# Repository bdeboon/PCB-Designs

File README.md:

# PCB-Designs
Repo for some of the open-source PCB's I have made over the years.

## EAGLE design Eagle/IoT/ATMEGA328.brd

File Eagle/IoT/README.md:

## IoT board for small wifi projects.

Board dimension = 2.5cm x 2.5cm, comes with wifi adapter, FTDI, USB C Connector for power with an onboard 3.3V regulator.
Assortment of pins can be used to control IoT devices

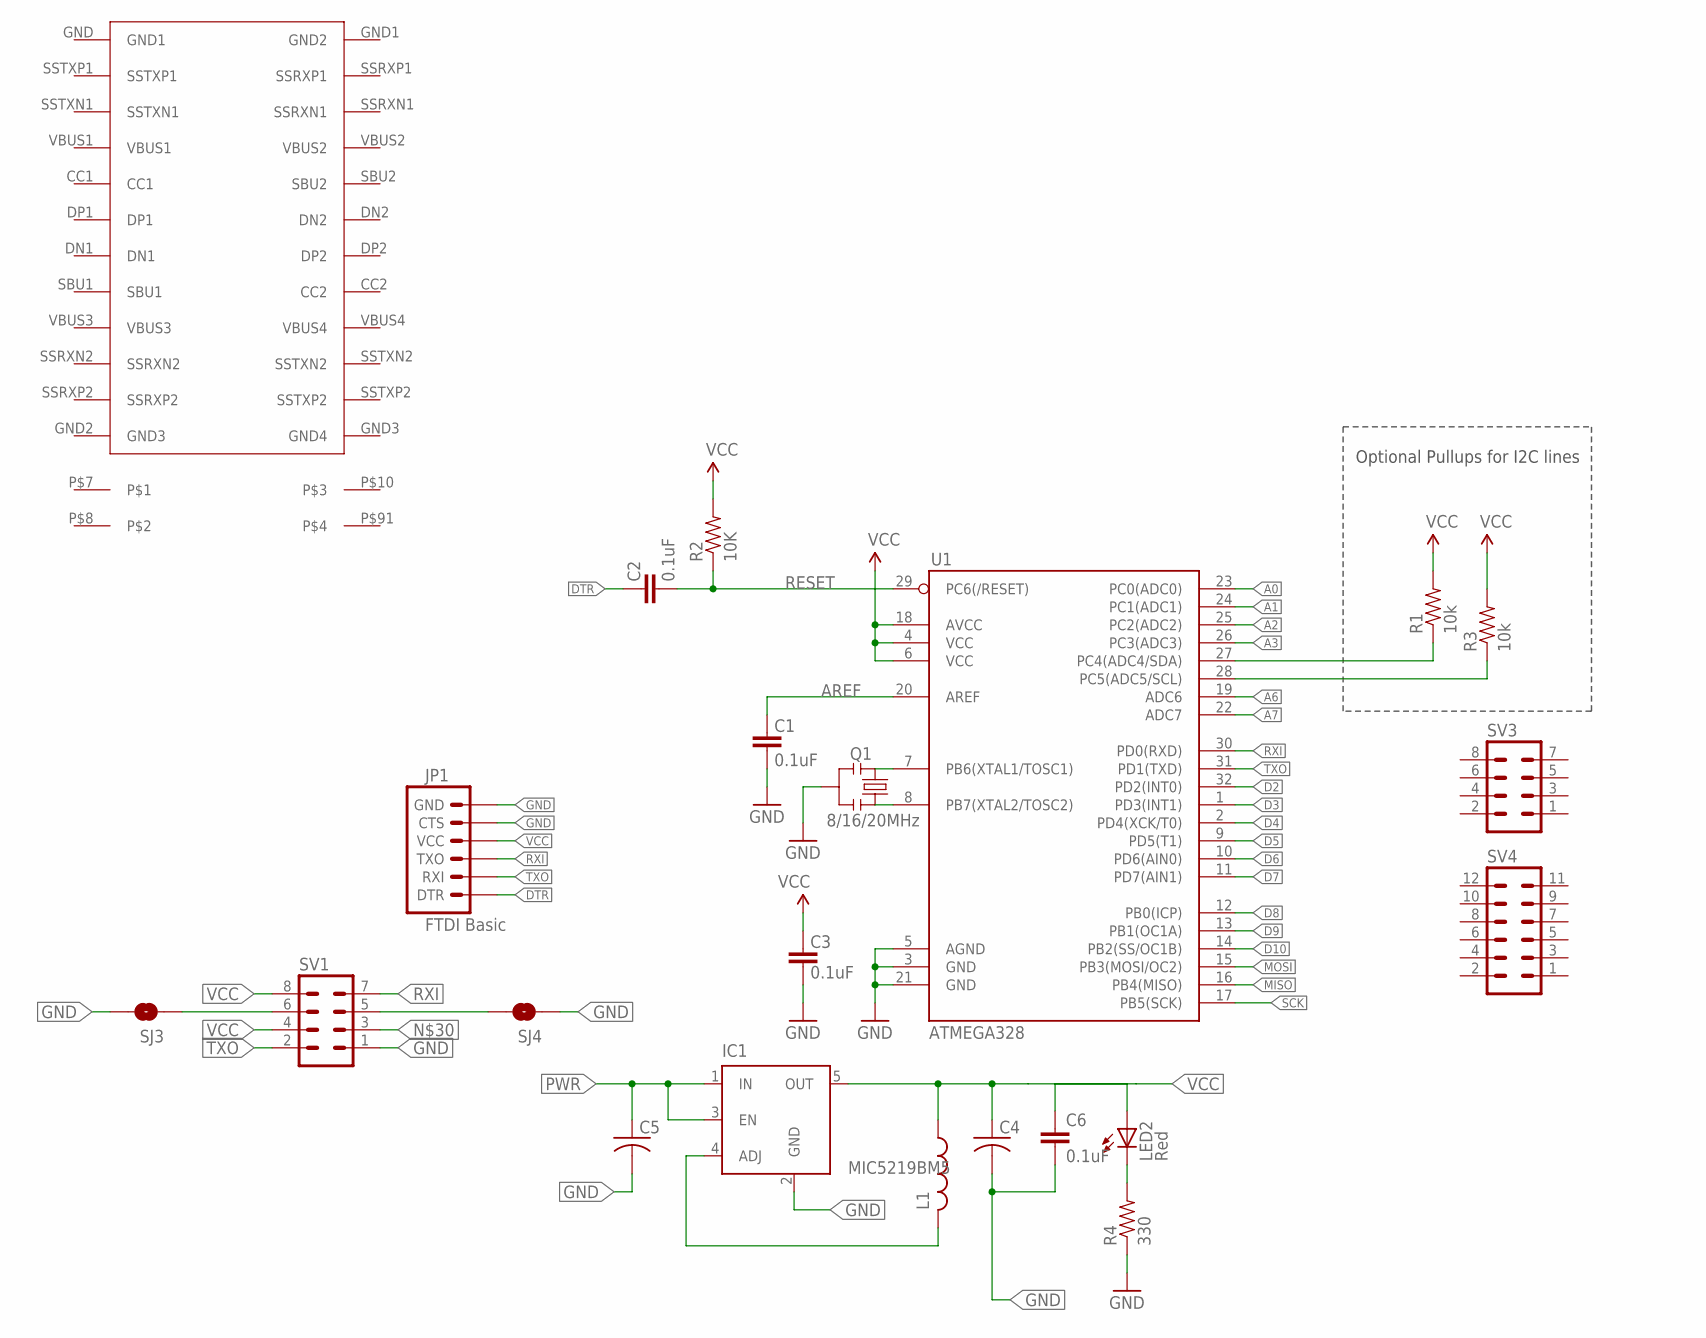
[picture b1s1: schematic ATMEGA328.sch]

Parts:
C1, C2, C3, C6: 0.1uF; 0603-CAP
C4, C5: C-USC0805K; C0805K
IC1: MIC5219BM5; SOT23-5
JP1: FTDI Basic; 1X06
L1: L-USL2012C; L2012C
LED2: Red; 0603-LED-ALT1
Q1: 8/16/20MHz; RESONATOR-SMD-1:1
R1, R3: 10k; 0603-RES
R2: 10K; 0603-RES
R4: 330; 0603-RES
SJ3, SJ4: SOLDERJUMPERNC; SJ_2S
SV1, SV3: MA04-2
SV4: MA06-2
U1: ATMEGA328; TQFP32-08
U$1: USB-C

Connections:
A0: U1.23 (PC0(ADC0))
A1: U1.24 (PC1(ADC1))
A2: U1.25 (PC2(ADC2))
A3: U1.26 (PC3(ADC3))
A4: R1.1, U1.27 (PC4(ADC4/SDA))
A5: R3.1, U1.28 (PC5(ADC5/SCL))
A6: U1.19 (ADC6)
A7: U1.22 (ADC7)
AREF: C1.2, U1.20 (AREF)
D2: U1.32 (PD2(INT0))
D3: U1.1 (PD3(INT1))
D4: U1.2 (PD4(XCK/T0))
D5: U1.9 (PD5(T1))
D6: U1.10 (PD6(AIN0))
D7: U1.11 (PD7(AIN1))
D8: U1.12 (PB0(ICP))
D9: U1.13 (PB1(OC1A))
D10: U1.14 (PB2(SS/OC1B))
DTR: C2.2, JP1.1 (DTR)
GND: C1.1, C3.1, C4.2, C5.2, C6.2, IC1.2 (GND), JP1.5 (CTS), JP1.6 (GND), Q1.2, R4.1, SJ3.2, SJ4.1, SV1.1, U1.3 (GND), U1.5 (AGND), U1.21 (GND)
MISO: U1.16 (PB4(MISO))
MOSI: U1.15 (PB3(MOSI/OC2))
unnamed: Q1.3, U1.8 (PB7(XTAL2/TOSC2))
unnamed: Q1.1, U1.7 (PB6(XTAL1/TOSC1))
unnamed: LED2.C, R4.2
unnamed: SJ4.2, SV1.5
unnamed: IC1.4 (ADJ), L1.2
PWR: C5.1, IC1.1 (IN), IC1.3 (EN)
RESET: C2.1, R2.1, U1.29 (PC6(/RESET))
RESET_WIFI: SJ3.1, SV1.6
RXI: JP1.3 (TXO), SV1.7, U1.30 (PD0(RXD))
SCK: U1.17 (PB5(SCK))
TXO: JP1.2 (RXI), SV1.2, U1.31 (PD1(TXD))
VCC: C3.2, C4.1, C6.1, IC1.5 (OUT), JP1.4 (VCC), L1.1, LED2.A, R1.2, R2.2, R3.2, SV1.4, SV1.8, U1.4 (VCC), U1.6 (VCC), U1.18 (AVCC)

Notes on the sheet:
Optional Pullups for I2C lines

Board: 2 copper layers, 22 parts (0 on the bottom side), 16 nets, no tracks yet.

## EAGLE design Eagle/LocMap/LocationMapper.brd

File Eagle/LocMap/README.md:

# Location Mapper PCB Version 1

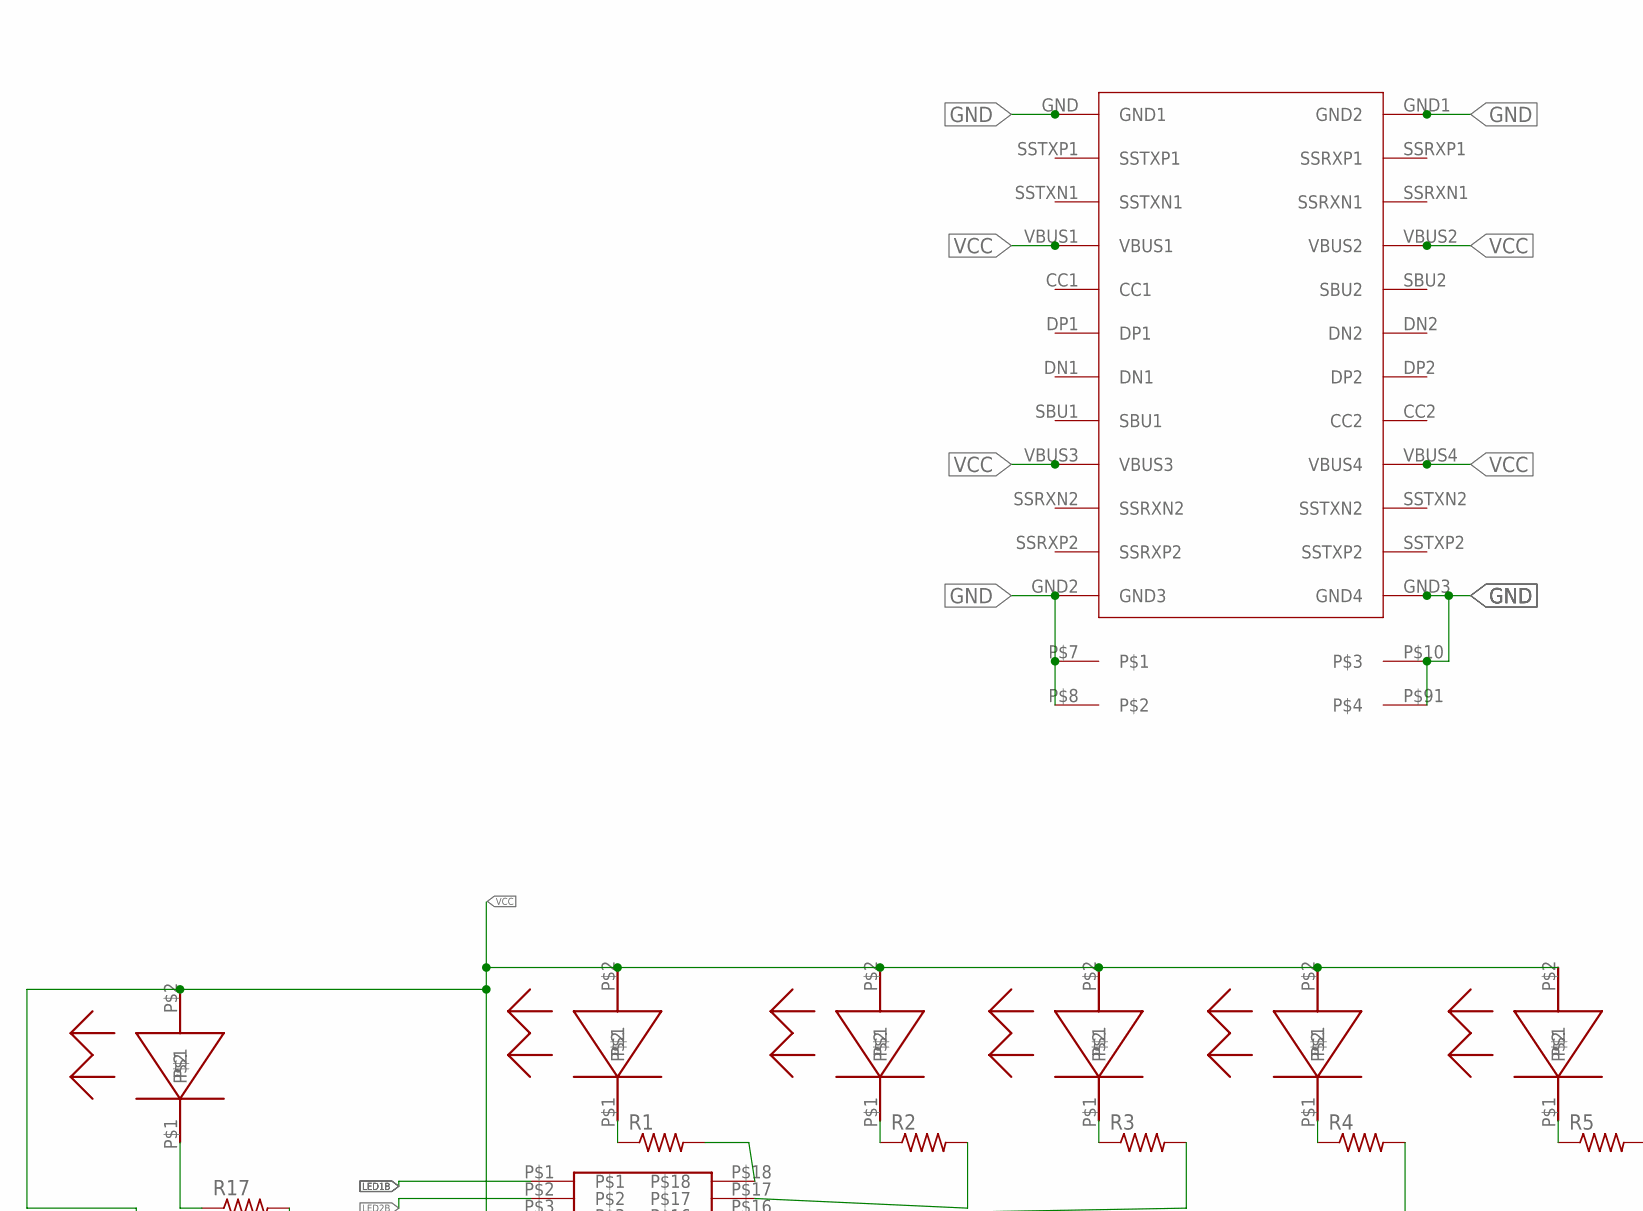
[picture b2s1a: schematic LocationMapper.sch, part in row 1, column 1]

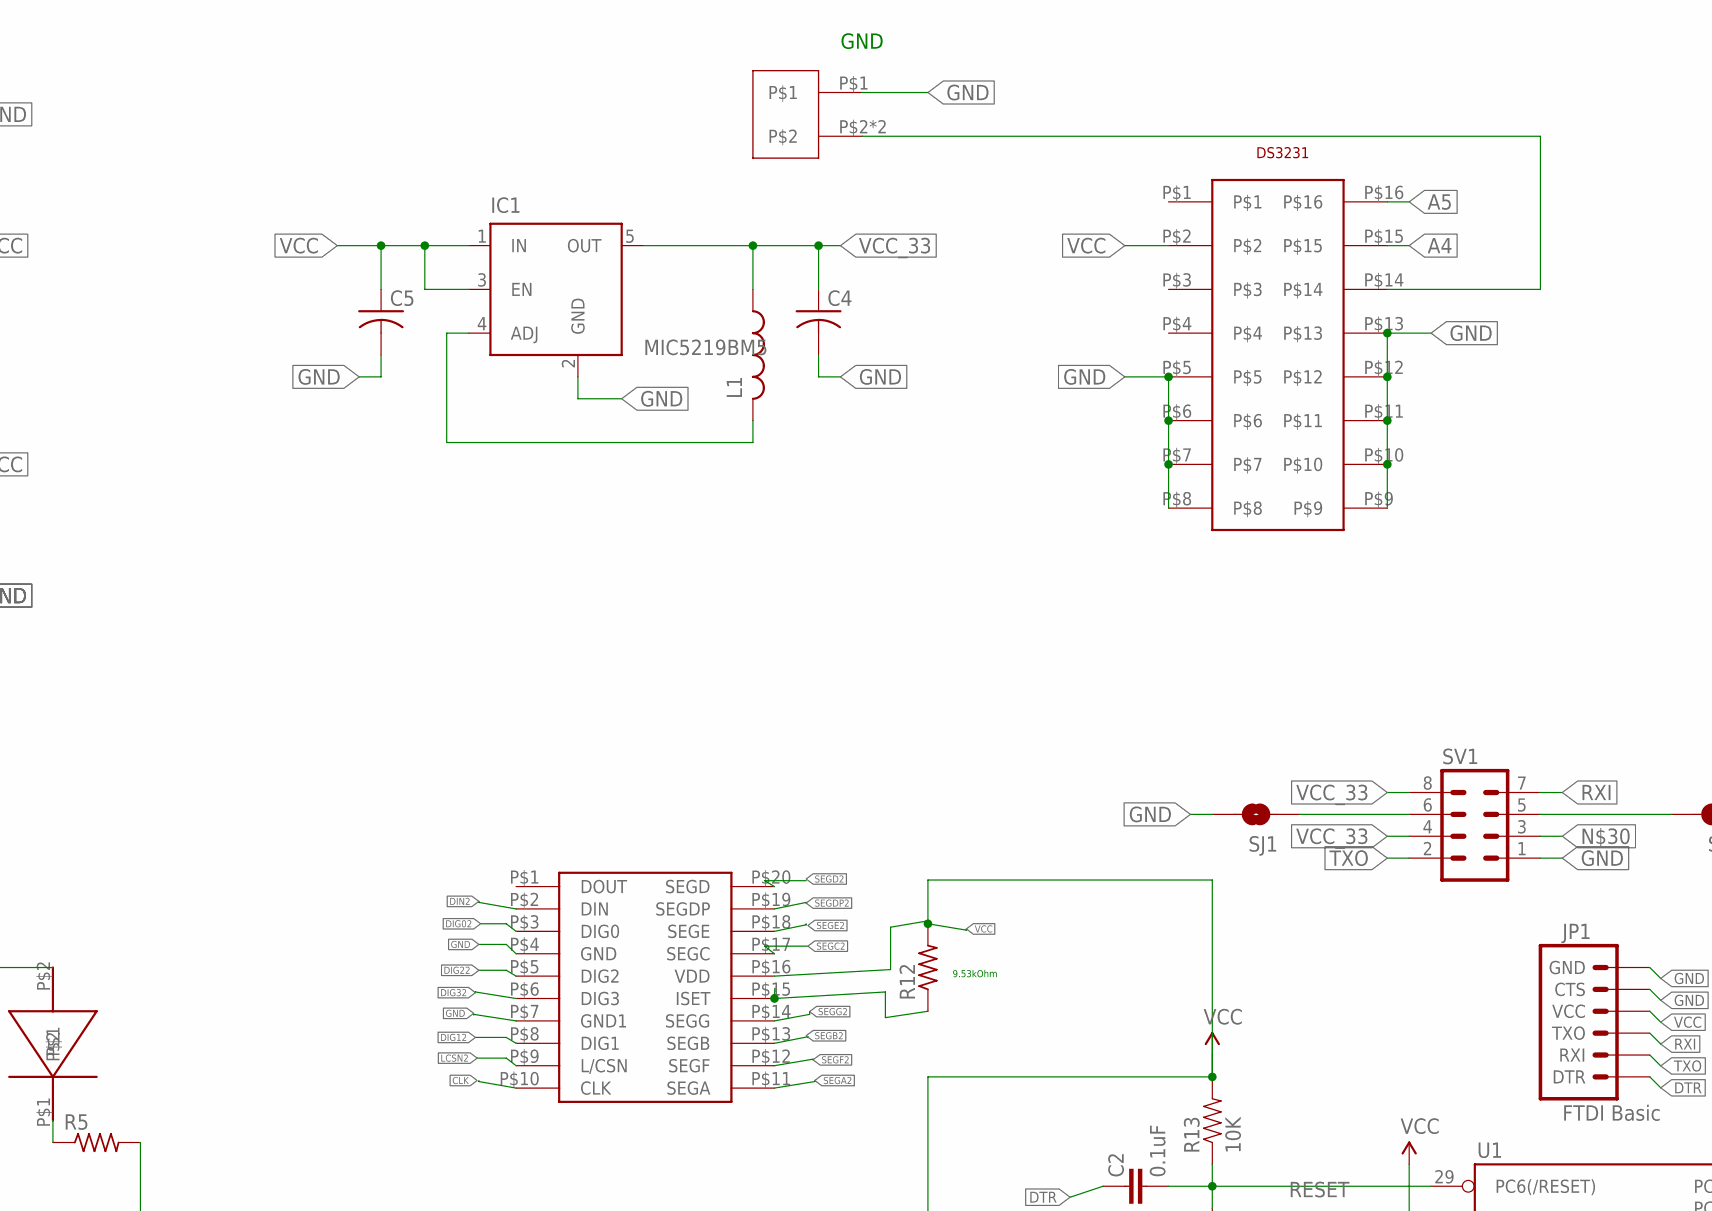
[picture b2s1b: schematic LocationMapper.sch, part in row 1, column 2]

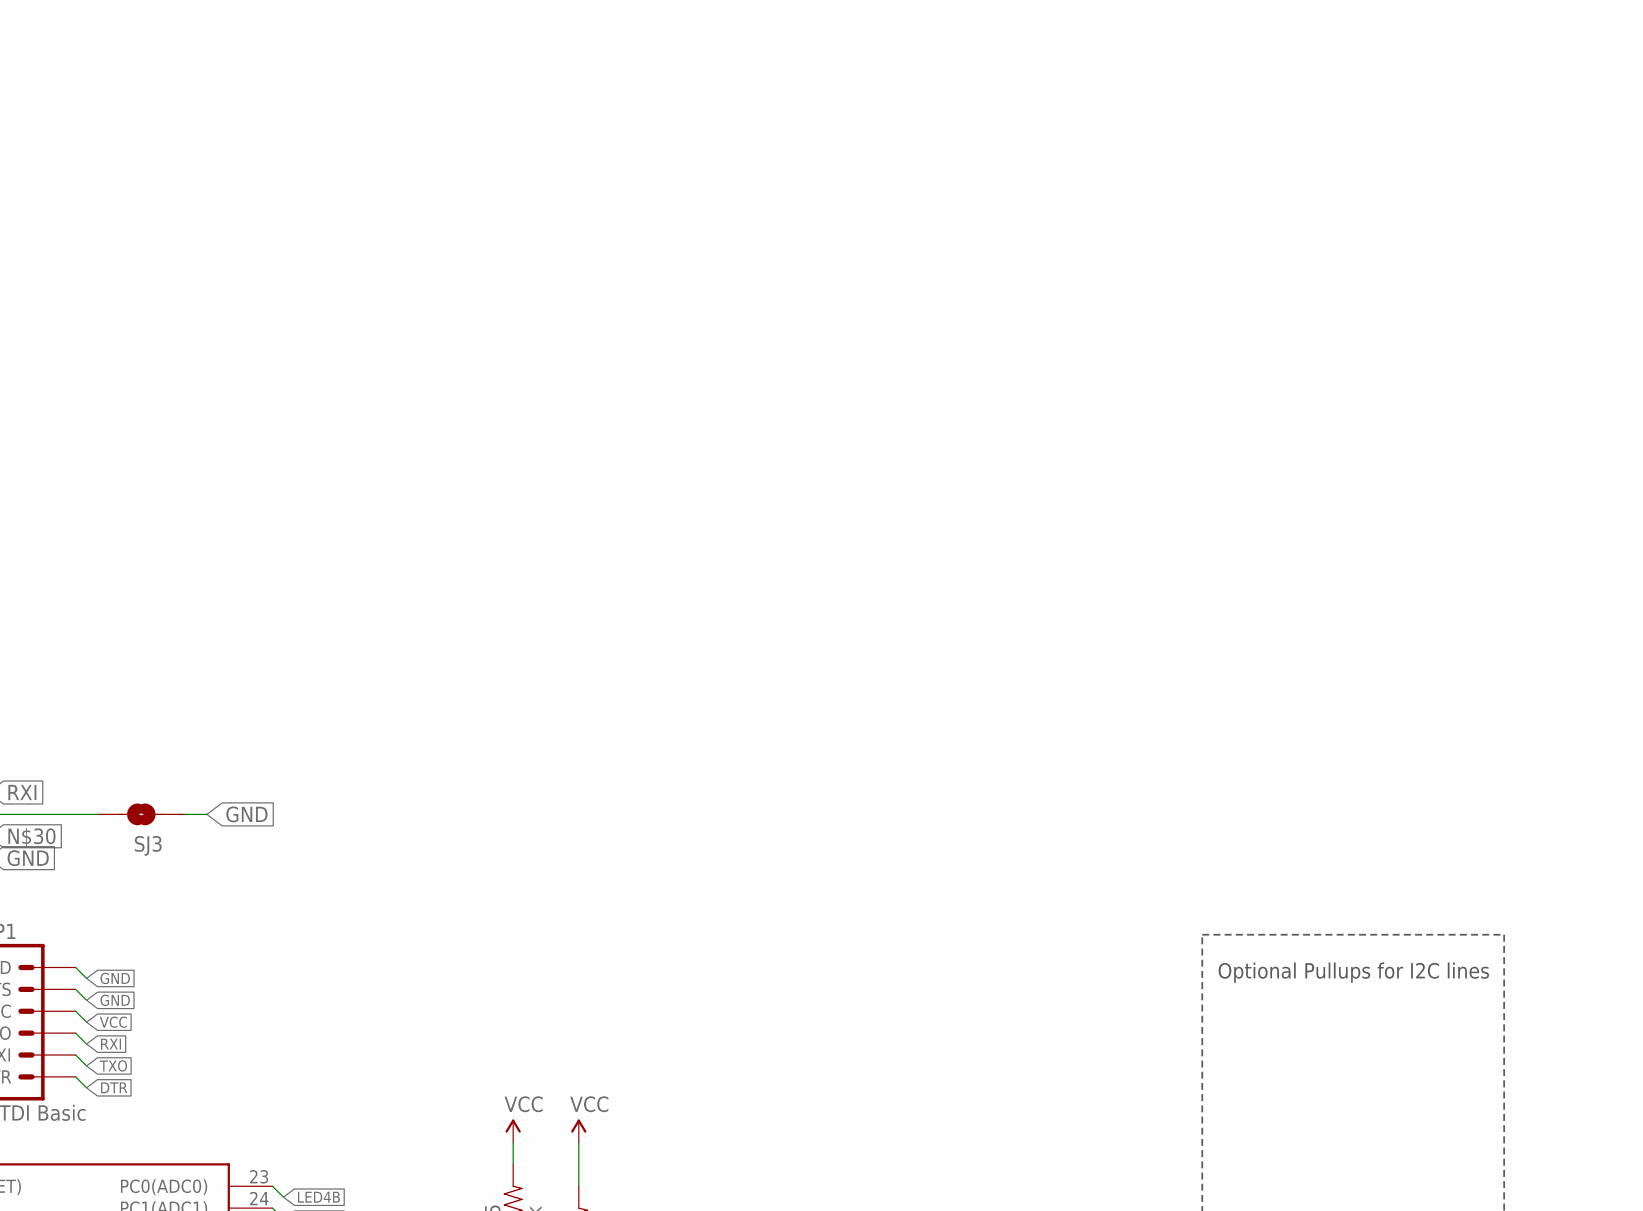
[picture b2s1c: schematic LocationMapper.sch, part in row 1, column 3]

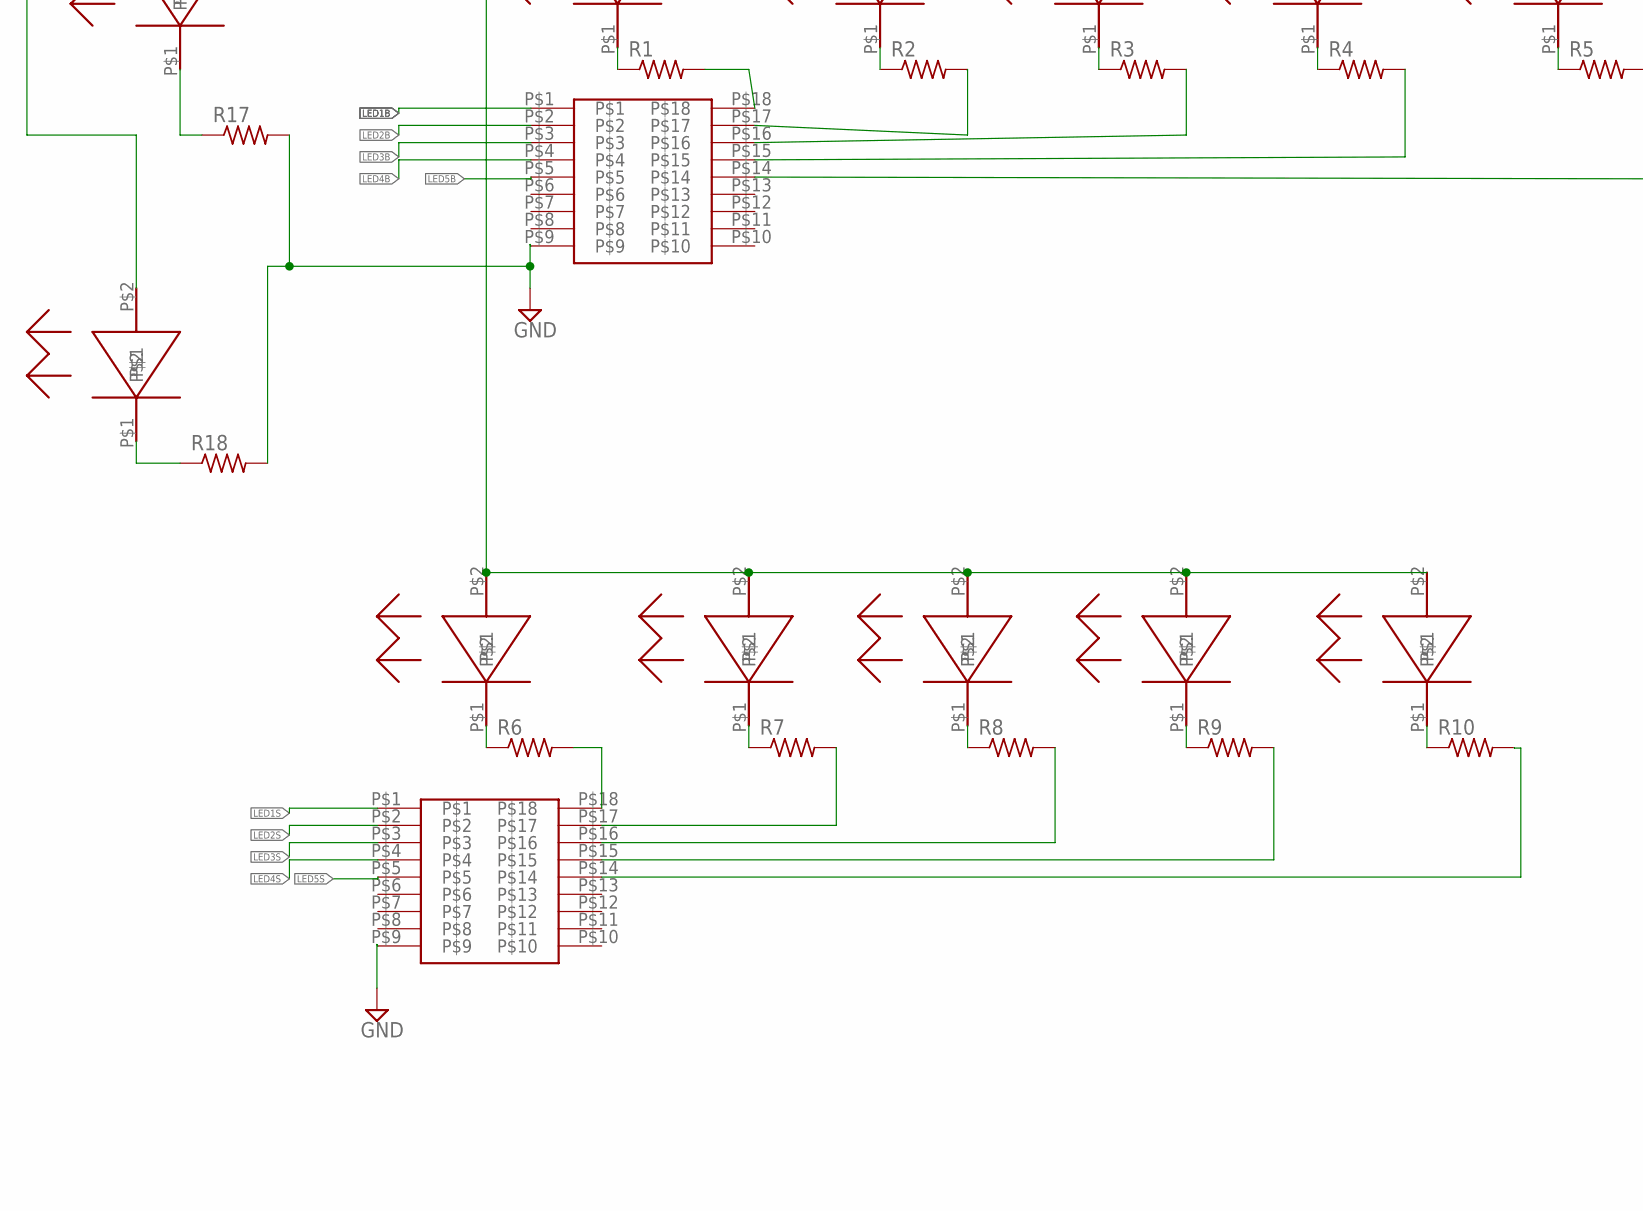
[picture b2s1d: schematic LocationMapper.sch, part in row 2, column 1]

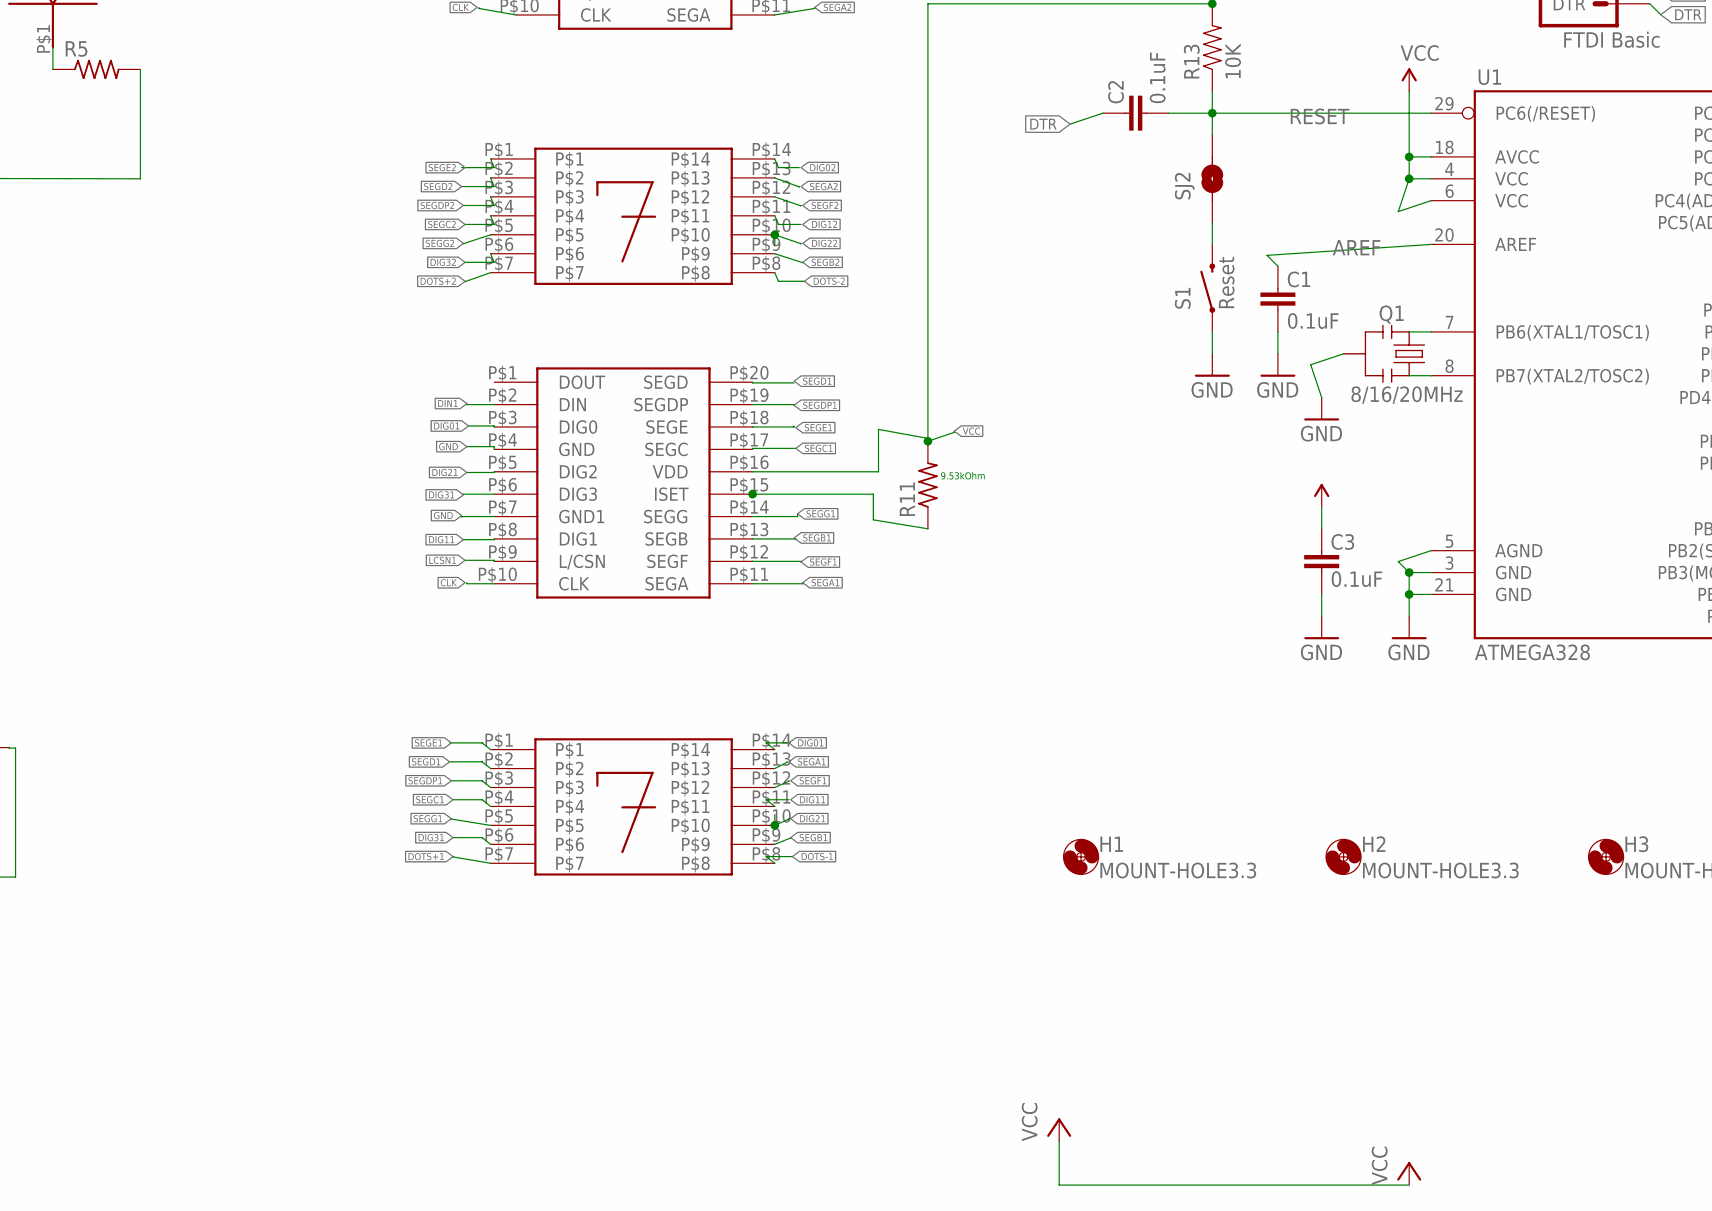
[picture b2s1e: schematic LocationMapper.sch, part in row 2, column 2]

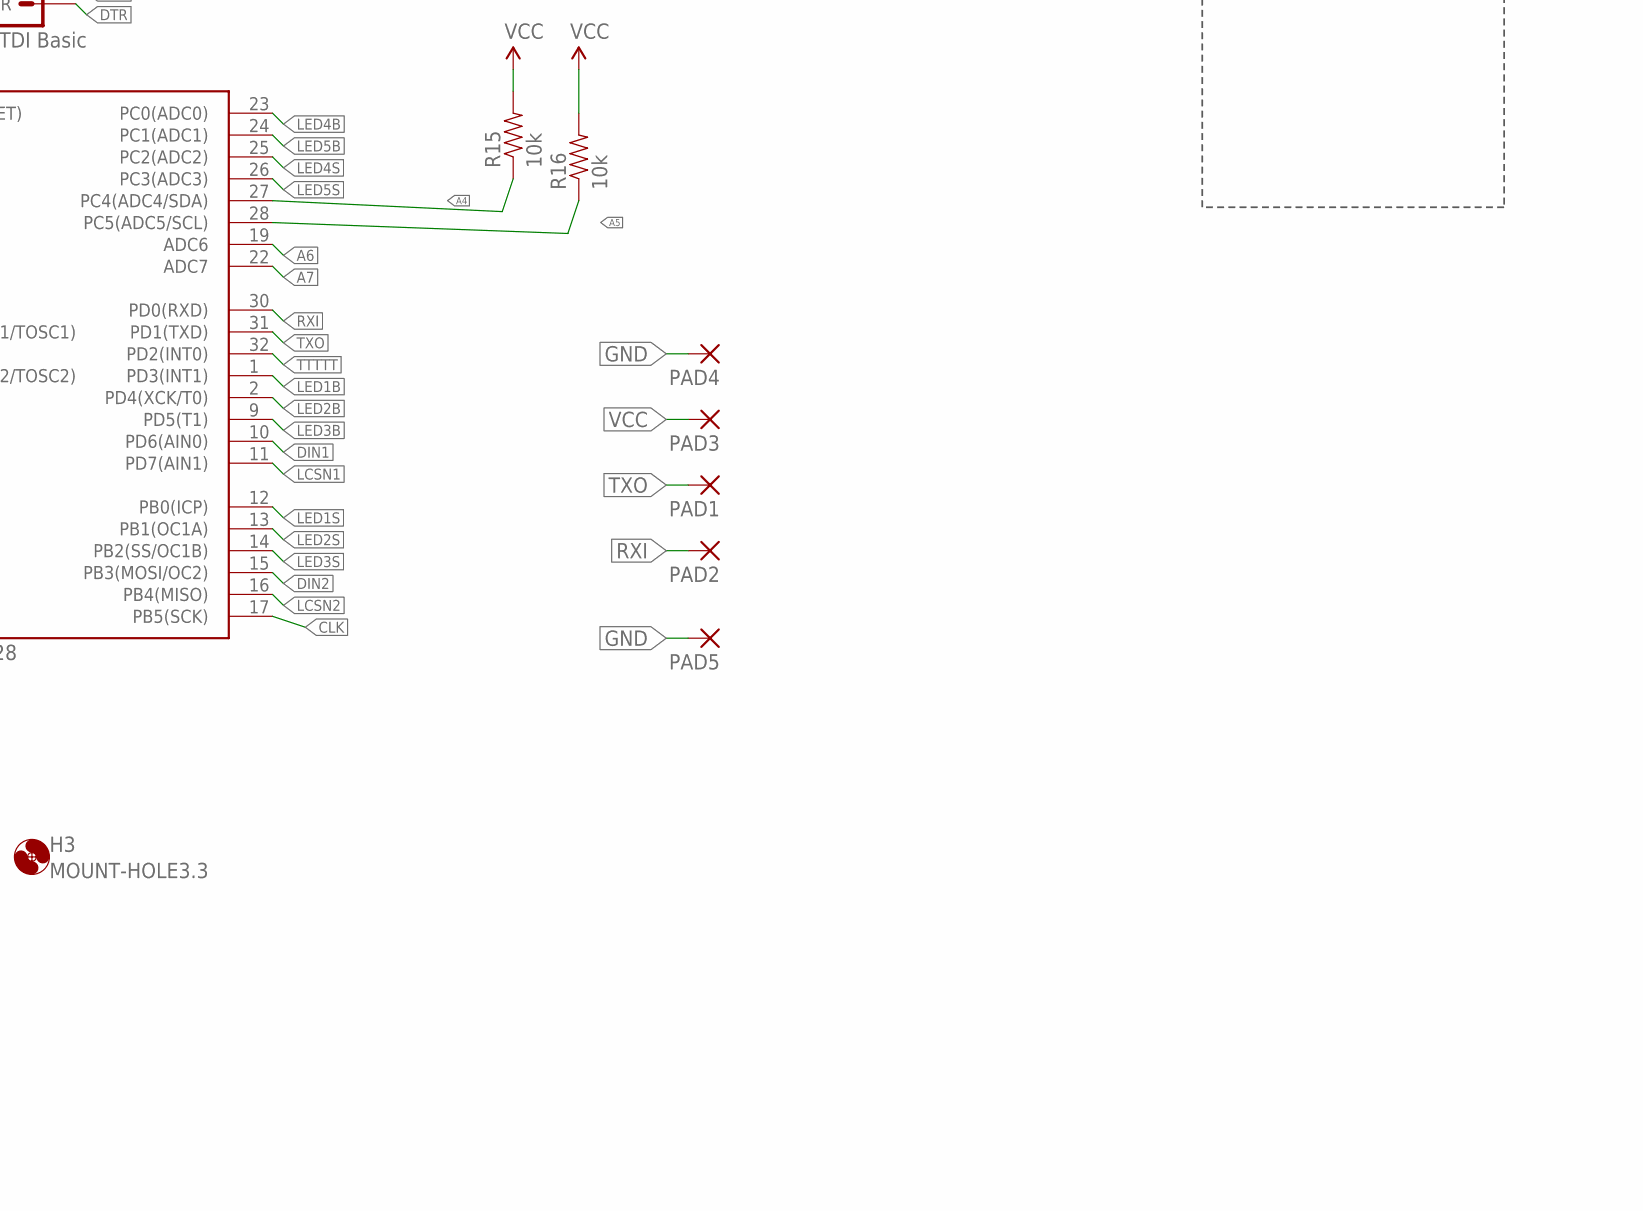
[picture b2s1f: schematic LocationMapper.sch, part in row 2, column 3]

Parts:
C1, C2, C3: 0.1uF; 0603-CAP
C4, C5: C-USC0805K; C0805K
H1, H2, H3: MOUNT-HOLE3.3; 3,3
IC1: MIC5219BM5; SOT23-5
JP1: FTDI Basic; 1X06
L1: L-USL2012C; L2012C
PAD1, PAD2, PAD3, PAD4, PAD5: 2,54/1,1
Q1: 8/16/20MHz; RESONATOR-SMD-1:1
R1, R2, R3, R4, R5, R6, R7, R8, R9, R10, R11, R12, R17, R18: R-US_R0805; R0805
R13: 10K; 0603-RES
R15, R16: 10k; 0603-RES
S1: Reset; TACTILE-SWITCH-SMD-ALT01
SJ1, SJ2, SJ3: SOLDERJUMPERNC; SJ_2S
SV1: MA04-2
U1: ATMEGA328; TQFP32-08
U$1, U$2, U$3, U$4, U$5, U$6, U$7, U$8, U$9, U$10, U$17, U$18: LED_LM
U$11, U$12: ULN2803A
U$13, U$14: 7SEG
U$15, U$16: 7SEG_DRIVER; SO20W
U$19: DS3231_BACK
U$20: CR2032
U$21: USB-C

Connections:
A4: R15.1, U1.27 (PC4(ADC4/SDA)), U$19.P$15
A5: R16.1, U1.28 (PC5(ADC5/SCL)), U$19.P$16
A6: U1.19 (ADC6)
A7: U1.22 (ADC7)
AREF: C1.2, U1.20 (AREF)
CLK: U1.17 (PB5(SCK)), U$15.P$10 (CLK), U$16.P$10 (CLK)
DIG01: U$14.P$14, U$15.P$3 (DIG0)
DIG02: U$13.P$14, U$16.P$3 (DIG0)
DIG11: U$14.P$11, U$15.P$8 (DIG1)
DIG12: U$13.P$11, U$16.P$8 (DIG1)
DIG21: U$14.P$10, U$15.P$5 (DIG2)
DIG22: U$13.P$10, U$16.P$5 (DIG2)
DIG31: U$14.P$6, U$15.P$6 (DIG3)
DIG32: U$13.P$6, U$16.P$6 (DIG3)
DIN1: U1.10 (PD6(AIN0)), U$15.P$2 (DIN)
DIN2: U1.15 (PB3(MOSI/OC2)), U$16.P$2 (DIN)
DOTS+1: U$14.P$7
DOTS+2: U$13.P$7
DOTS-1: U$14.P$8
DOTS-2: U$13.P$8
DTR: C2.2, JP1.1 (DTR)
GND: C1.1, C3.1, C4.2, C5.2, IC1.2 (GND), JP1.5 (CTS), JP1.6 (GND), PAD4.1, PAD5.1, Q1.2, R17.2, R18.2, S1.1, S1.2 (1), SJ1.2, SJ3.1, SV1.1, U1.3 (GND), U1.5 (AGND), U1.21 (GND), U$11.P$9, U$12.P$9, U$15.P$4 (GND), U$15.P$7 (GND1), U$16.P$4 (GND), U$16.P$7 (GND1), U$19.P$5, U$19.P$6, U$19.P$7, U$19.P$8, U$19.P$9, U$19.P$10, U$19.P$11, U$19.P$12, U$19.P$13, U$20.P$1, U$21.GND (GND1), U$21.GND1 (GND2), U$21.GND2 (GND3), U$21.GND3 (GND4), U$21.P$7, U$21.P$8, U$21.P$10, U$21.P$91
LCSN1: U1.11 (PD7(AIN1)), U$15.P$9 (L/CSN)
LCSN2: U1.16 (PB4(MISO)), U$16.P$9 (L/CSN)
LED1B: U1.1 (PD3(INT1)), U$11.P$1
LED1S: U1.12 (PB0(ICP)), U$12.P$1
LED2B: U1.2 (PD4(XCK/T0)), U$11.P$2
LED2S: U1.13 (PB1(OC1A)), U$12.P$2
LED3B: U1.9 (PD5(T1)), U$11.P$3
LED3S: U1.14 (PB2(SS/OC1B)), U$12.P$3
LED4B: U1.23 (PC0(ADC0)), U$11.P$4
LED4S: U1.25 (PC2(ADC2)), U$12.P$4
LED5B: U1.24 (PC1(ADC1)), U$11.P$5
LED5S: U1.26 (PC3(ADC3)), U$12.P$5
unnamed: R1.1, U$6.P$1
unnamed: R2.1, U$7.P$1
unnamed: R3.1, U$8.P$1
unnamed: R4.1, U$9.P$1
unnamed: R5.1, U$10.P$1
unnamed: R6.1, U$1.P$1
unnamed: R7.1, U$2.P$1
unnamed: R8.1, U$3.P$1
unnamed: R9.1, U$4.P$1
unnamed: R10.1, U$5.P$1
unnamed: U$19.P$14, U$20.P$2, U$20.P$3
unnamed: R1.2, U$11.P$18
unnamed: R2.2, U$11.P$17
unnamed: R3.2, U$11.P$16
unnamed: R4.2, U$11.P$15
unnamed: R5.2, U$11.P$14
unnamed: R6.2, U$12.P$18
unnamed: R7.2, U$12.P$17
unnamed: R8.2, U$12.P$16
unnamed: R9.2, U$12.P$15
unnamed: R10.2, U$12.P$14
unnamed: R18.1, U$18.P$1
unnamed: R12.1, U$16.P$15 (ISET)
unnamed: Q1.3, U1.8 (PB7(XTAL2/TOSC2))
unnamed: Q1.1, U1.7 (PB6(XTAL1/TOSC1))
unnamed: S1.3 (2), S1.4 (2), SJ2.1
unnamed: R17.1, U$17.P$1
unnamed: SJ3.2, SV1.5
unnamed: IC1.4 (ADJ), L1.2
unnamed: R11.1, U$15.P$15 (ISET)
RESET: C2.1, R13.1, SJ2.2, U1.29 (PC6(/RESET))
RESET_WIFI: SJ1.1, SV1.6
RXI: JP1.3 (TXO), PAD2.1, SV1.7, U1.30 (PD0(RXD))
SEGA1: U$14.P$13, U$15.P$11 (SEGA)
SEGA2: U$13.P$13, U$16.P$11 (SEGA)
SEGB1: U$14.P$9, U$15.P$13 (SEGB)
SEGB2: U$13.P$9, U$16.P$13 (SEGB)
SEGC1: U$14.P$4, U$15.P$17 (SEGC)
SEGC2: U$13.P$4, U$16.P$17 (SEGC)
SEGD1: U$14.P$2, U$15.P$20 (SEGD)
SEGD2: U$13.P$2, U$16.P$20 (SEGD)
SEGDP1: U$14.P$3, U$15.P$19 (SEGDP)
SEGDP2: U$13.P$3, U$16.P$19 (SEGDP)
SEGE1: U$14.P$1, U$15.P$18 (SEGE)
SEGE2: U$13.P$1, U$16.P$18 (SEGE)
SEGF1: U$14.P$12, U$15.P$12 (SEGF)
SEGF2: U$13.P$12, U$16.P$12 (SEGF)
SEGG1: U$14.P$5, U$15.P$14 (SEGG)
SEGG2: U$13.P$5, U$16.P$14 (SEGG)
TTTTT: U1.32 (PD2(INT0))
TXO: JP1.2 (RXI), PAD1.1, SV1.2, U1.31 (PD1(TXD))
VCC: C3.2, C5.1, IC1.1 (IN), IC1.3 (EN), JP1.4 (VCC), PAD3.1, R11.2, R12.2, R13.2, R15.2, R16.2, U1.4 (VCC), U1.6 (VCC), U1.18 (AVCC), U$1.P$2, U$2.P$2, U$3.P$2, U$4.P$2, U$5.P$2, U$6.P$2, U$7.P$2, U$8.P$2, U$9.P$2, U$10.P$2, U$15.P$16 (VDD), U$16.P$16 (VDD), U$17.P$2, U$18.P$2, U$19.P$2, U$21.VBUS1, U$21.VBUS2, U$21.VBUS3, U$21.VBUS4
VCC_33: C4.1, IC1.5 (OUT), L1.1, SV1.4, SV1.8

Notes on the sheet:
9.53kOhm
Optional Pullups for I2C lines
GND

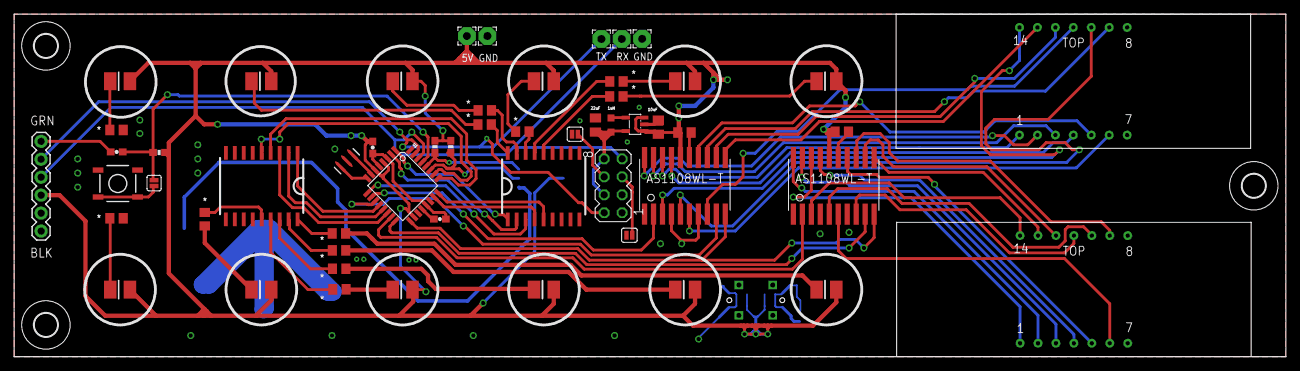
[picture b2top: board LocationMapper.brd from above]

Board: 2 copper layers, 180.0 x 48.5 mm, 61 parts (0 on the bottom side), 80 nets.

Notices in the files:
parts and their libraries:
SparkFun-Boards: Licensing: Creative Commons ShareAlike 4.0 International - https://creativecommons.org/licenses/by-sa/4.0
SparkFun-Passives: Licensing: CC v3.0 Share-Alike You are welcome to use this library for commercial purposes.
